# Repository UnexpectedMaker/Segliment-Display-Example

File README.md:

# Segliment-Display

As promised, I have open sourced my version of the Segliment Display that I made as a joint project with David Watts

The repositry includes thw following folders

EAGLE - All Eagle CAD files (v9.2)

GERBERS - All gerber files

SEGLIMENT_DISPLAY_EXAMPLE - Example Arduino code

Plus there is a PDF Schematic and BOM

Here are some Affiliate & Non-Affiliate links to some of the parts I am using..

COB LED Filaments 

http://s.click.aliexpress.com/e/H0sUjrw

MCP23017SP2 GPIO Port Expander

https://www.aliexpress.com/item/10PCS-MCP23017-E-SP-DIP-28-MCP23017-16-Bit-I-O-Expander-with-I2C-Interface-IC/32866049803.html?spm=a2g0s.9042311.0.0.27424c4d2SrnUA

10k Network Resistor

http://s.click.aliexpress.com/e/cFmRmzUk

Enjoy!

# Buy me a coffee or back me on Patreon?
I love making and designing projects but sharing open source projects takes a lot of thought and time. I do it because I think it’s important to share knowledge and give back to the community like many have done before me.

If you find this project useful or want to see more open source projects like it, please consider buying me a coffee or backing me on Patreon to say thanks!

# Unexpected Maker
http://youtube.com/c/unexpectedmaker

http://twitter.com/unexpectedmaker

https://www.facebook.com/unexpectedmaker/

https://www.instagram.com/unexpectedmaker/

https://www.tindie.com/stores/seonr/

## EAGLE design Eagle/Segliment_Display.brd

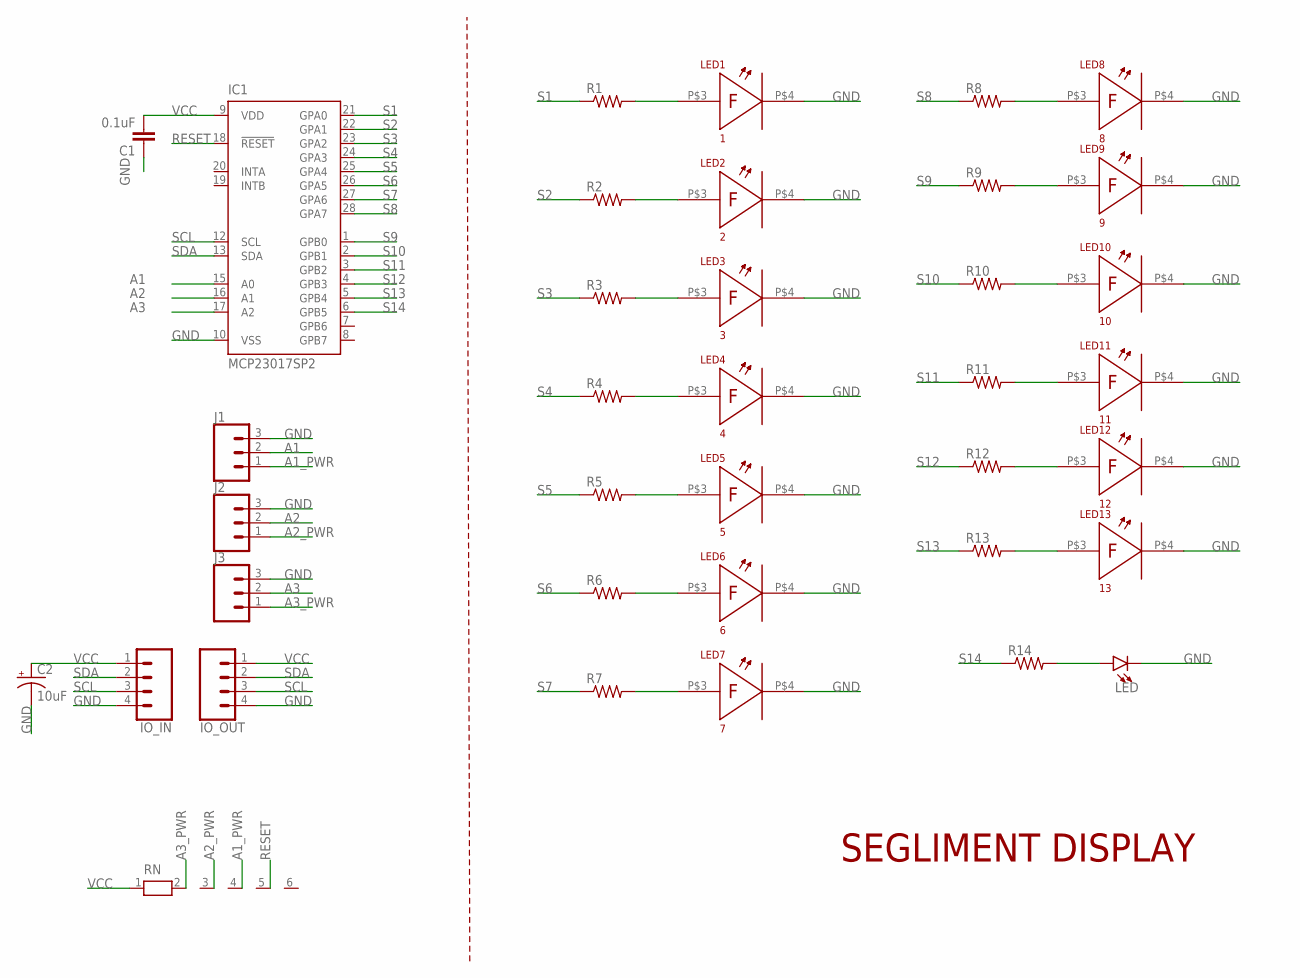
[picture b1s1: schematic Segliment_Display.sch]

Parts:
C1: 0.1uF; CAP-PTH-SMALL-KIT
C2: 10uF; CPOL-RADIAL-2.5MM-5MM
IC1: MCP23017SP2; DIL28-3-ROUND
IO_IN: CONN_041X04_NO_SILK; 1X04_NO_SILK
IO_OUT: CONN_041X04_NO_SILK; 1X04_NO_SILK
J1, J2, J3: CONN_031X03_NO_SILK; 1X03_NO_SILK
LED: LED3MM; LED_3MM
LED1: 1; RAISED
LED2: 2; RAISED
LED3: 3; RAISED
LED4: 4; RAISED
LED5: 5; RAISED
LED6: 6; RAISED
LED7: 7; RAISED
LED8: 8; RAISED
LED9: 9; RAISED
LED10: 10; RAISED
LED11: 11; RAISED
LED12: 12; RAISED
LED13: 13; RAISED
R1, R2, R3, R4, R5, R6, R7, R8, R9, R10, R11, R12, R13, R14: R-US_0207/7; 0207/7
RN: RN05; RN-6

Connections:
A1: IC1.15 (A0), J1.2
A1_PWR: J1.1, RN.4
A2: IC1.16 (A1), J2.2
A2_PWR: J2.1, RN.3
A3: IC1.17 (A2), J3.2
A3_PWR: J3.1, RN.2
GND: C1.1, C2.2 (-), IC1.10 (VSS), IO_IN.4, IO_OUT.4, J1.3, J2.3, J3.3, LED.K (C), LED1.P$4, LED2.P$4, LED3.P$4, LED4.P$4, LED5.P$4, LED6.P$4, LED7.P$4, LED8.P$4, LED9.P$4, LED10.P$4, LED11.P$4, LED12.P$4, LED13.P$4
unnamed: LED1.P$3, R1.2
unnamed: LED.A, R14.2
unnamed: LED2.P$3, R2.2
unnamed: LED3.P$3, R3.2
unnamed: LED4.P$3, R4.2
unnamed: LED5.P$3, R5.2
unnamed: LED6.P$3, R6.2
unnamed: LED7.P$3, R7.2
unnamed: LED8.P$3, R8.2
unnamed: LED9.P$3, R9.2
unnamed: LED10.P$3, R10.2
unnamed: LED11.P$3, R11.2
unnamed: LED12.P$3, R12.2
unnamed: LED13.P$3, R13.2
RESET: IC1.18 (!RESET), RN.5
S1: IC1.21 (GPA0), R1.1
S2: IC1.22 (GPA1), R2.1
S3: IC1.23 (GPA2), R3.1
S4: IC1.24 (GPA3), R4.1
S5: IC1.25 (GPA4), R5.1
S6: IC1.26 (GPA5), R6.1
S7: IC1.27 (GPA6), R7.1
S8: IC1.28 (GPA7), R8.1
S9: IC1.1 (GPB0), R9.1
S10: IC1.2 (GPB1), R10.1
S11: IC1.3 (GPB2), R11.1
S12: IC1.4 (GPB3), R12.1
S13: IC1.5 (GPB4), R13.1
S14: IC1.6 (GPB5), R14.1
SCL: IC1.12 (SCL), IO_IN.3, IO_OUT.3
SDA: IC1.13 (SDA), IO_IN.2, IO_OUT.2
VCC: C1.2, C2.1 (+), IC1.9 (VDD), IO_IN.1, IO_OUT.1, RN.1

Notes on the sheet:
SEGLIMENT DISPLAY

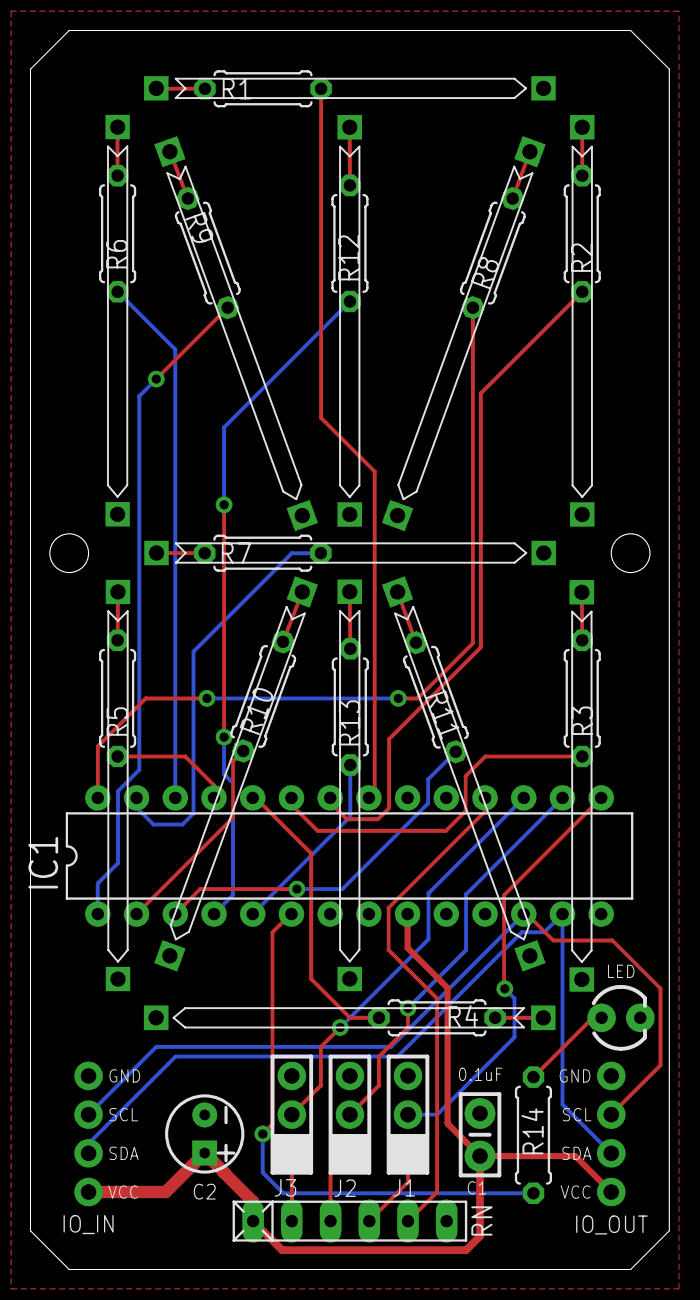
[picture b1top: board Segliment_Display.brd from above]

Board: 2 copper layers, 41.9 x 81.3 mm, 37 parts (0 on the bottom side), 39 nets.

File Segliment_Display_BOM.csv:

Partlist exported from /Users/seon/Dropbox/EagleCAD/projects/Siglement Display/Siglement 2018-2/Segliment_Display.sch at 11/10/18 4:24 PM

Part   Value       Device                          Package               Description                                                                                                     
C1     0.1uF       0.1UF-KIT-EZ-50V-20%            CAP-PTH-SMALL-KIT     0.1µF ceramic capacitors                                                                                        
C2     10uF        10UF-POLAR-RADIAL-2.5MM-25V-20% CPOL-RADIAL-2.5MM-5MM 10.0µF polarized capacitors                                                                                     
IC1    MCP23017SP2 MCP23017SP2                     DIL28-3-ROUND         hMCP23017SP2 GPIO Expander                                                   
IO_IN              CONN_041X04_NO_SILK             1X04_NO_SILK          0.254mm 4 pin header
IO_OUT             CONN_041X04_NO_SILK             1X04_NO_SILK          0.254mm 4 pin header
J1                 CONN_031X03_NO_SILK             1X03_NO_SILK        	 0.254mm 3 pin header
J2                 CONN_031X03_NO_SILK             1X03_NO_SILK          0.254mm 3 pin header
J3                 CONN_031X03_NO_SILK             1X03_NO_SILK          0.254mm 3 pin header 
LED                LED3MM                          LED_3MM               3mm Yellow LED                                                                                                 
LED1   1           LED28-30MMRAISED                RAISED                This is a filament LED                                                                                          
LED2   2           LED28-30MMRAISED                RAISED                This is a filament LED                                                                                          
LED3   3           LED28-30MMRAISED                RAISED                This is a filament LED                                                                                          
LED4   4           LED28-30MMRAISED                RAISED                This is a filament LED                                                                                          
LED5   5           LED28-30MMRAISED                RAISED                This is a filament LED                                                                                          
LED6   6           LED28-30MMRAISED                RAISED                This is a filament LED                                                                                          
LED7   7           LED28-30MMRAISED                RAISED                This is a filament LED                                                                                          
LED8   8           LED28-30MMRAISED                RAISED                This is a filament LED                                                                                          
LED9   9           LED28-30MMRAISED                RAISED                This is a filament LED                                                                                          
LED10  10          LED28-30MMRAISED                RAISED                This is a filament LED                                                                                          
LED11  11          LED28-30MMRAISED                RAISED                This is a filament LED                                                                                          
LED12  12          LED28-30MMRAISED                RAISED                This is a filament LED                                                                                          
LED13  13          LED28-30MMRAISED                RAISED                This is a filament LED                                                                                          
R1                 R-US_0207/7                     0207/7                100R                                                                                    
R2                 R-US_0207/7                     0207/7                100R                                                                                   
R3                 R-US_0207/7                     0207/7                100R                                                                                    
R4                 R-US_0207/7                     0207/7                100R                                                                                    
R5                 R-US_0207/7                     0207/7                100R                                                                                    
R6                 R-US_0207/7                     0207/7                100R                                                                                    
R7                 R-US_0207/7                     0207/7                100R                                                                                    
R8                 R-US_0207/7                     0207/7                100R                                                                                    
R9                 R-US_0207/7                     0207/7                100R                                                                                    
R10                R-US_0207/7                     0207/7                100R                                                                                    
R11                R-US_0207/7                     0207/7                100R                                                                                    
R12                R-US_0207/7                     0207/7                100R                                                                                    
R13                R-US_0207/7                     0207/7                100R                                                                                    
R14                R-US_0207/7                     0207/7                220R                                                                                    
RN                 RN05                            RN-6                  10K RESISTOR NETWORK

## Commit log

2018-10-11 Added all CAD design files, Schematic PDF and BOM

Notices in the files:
parts and their libraries:
SparkFun-Connectors: Licensing: Creative Commons ShareAlike 4.0 International - https://creativecommons.org/licenses/by-sa/4.0
